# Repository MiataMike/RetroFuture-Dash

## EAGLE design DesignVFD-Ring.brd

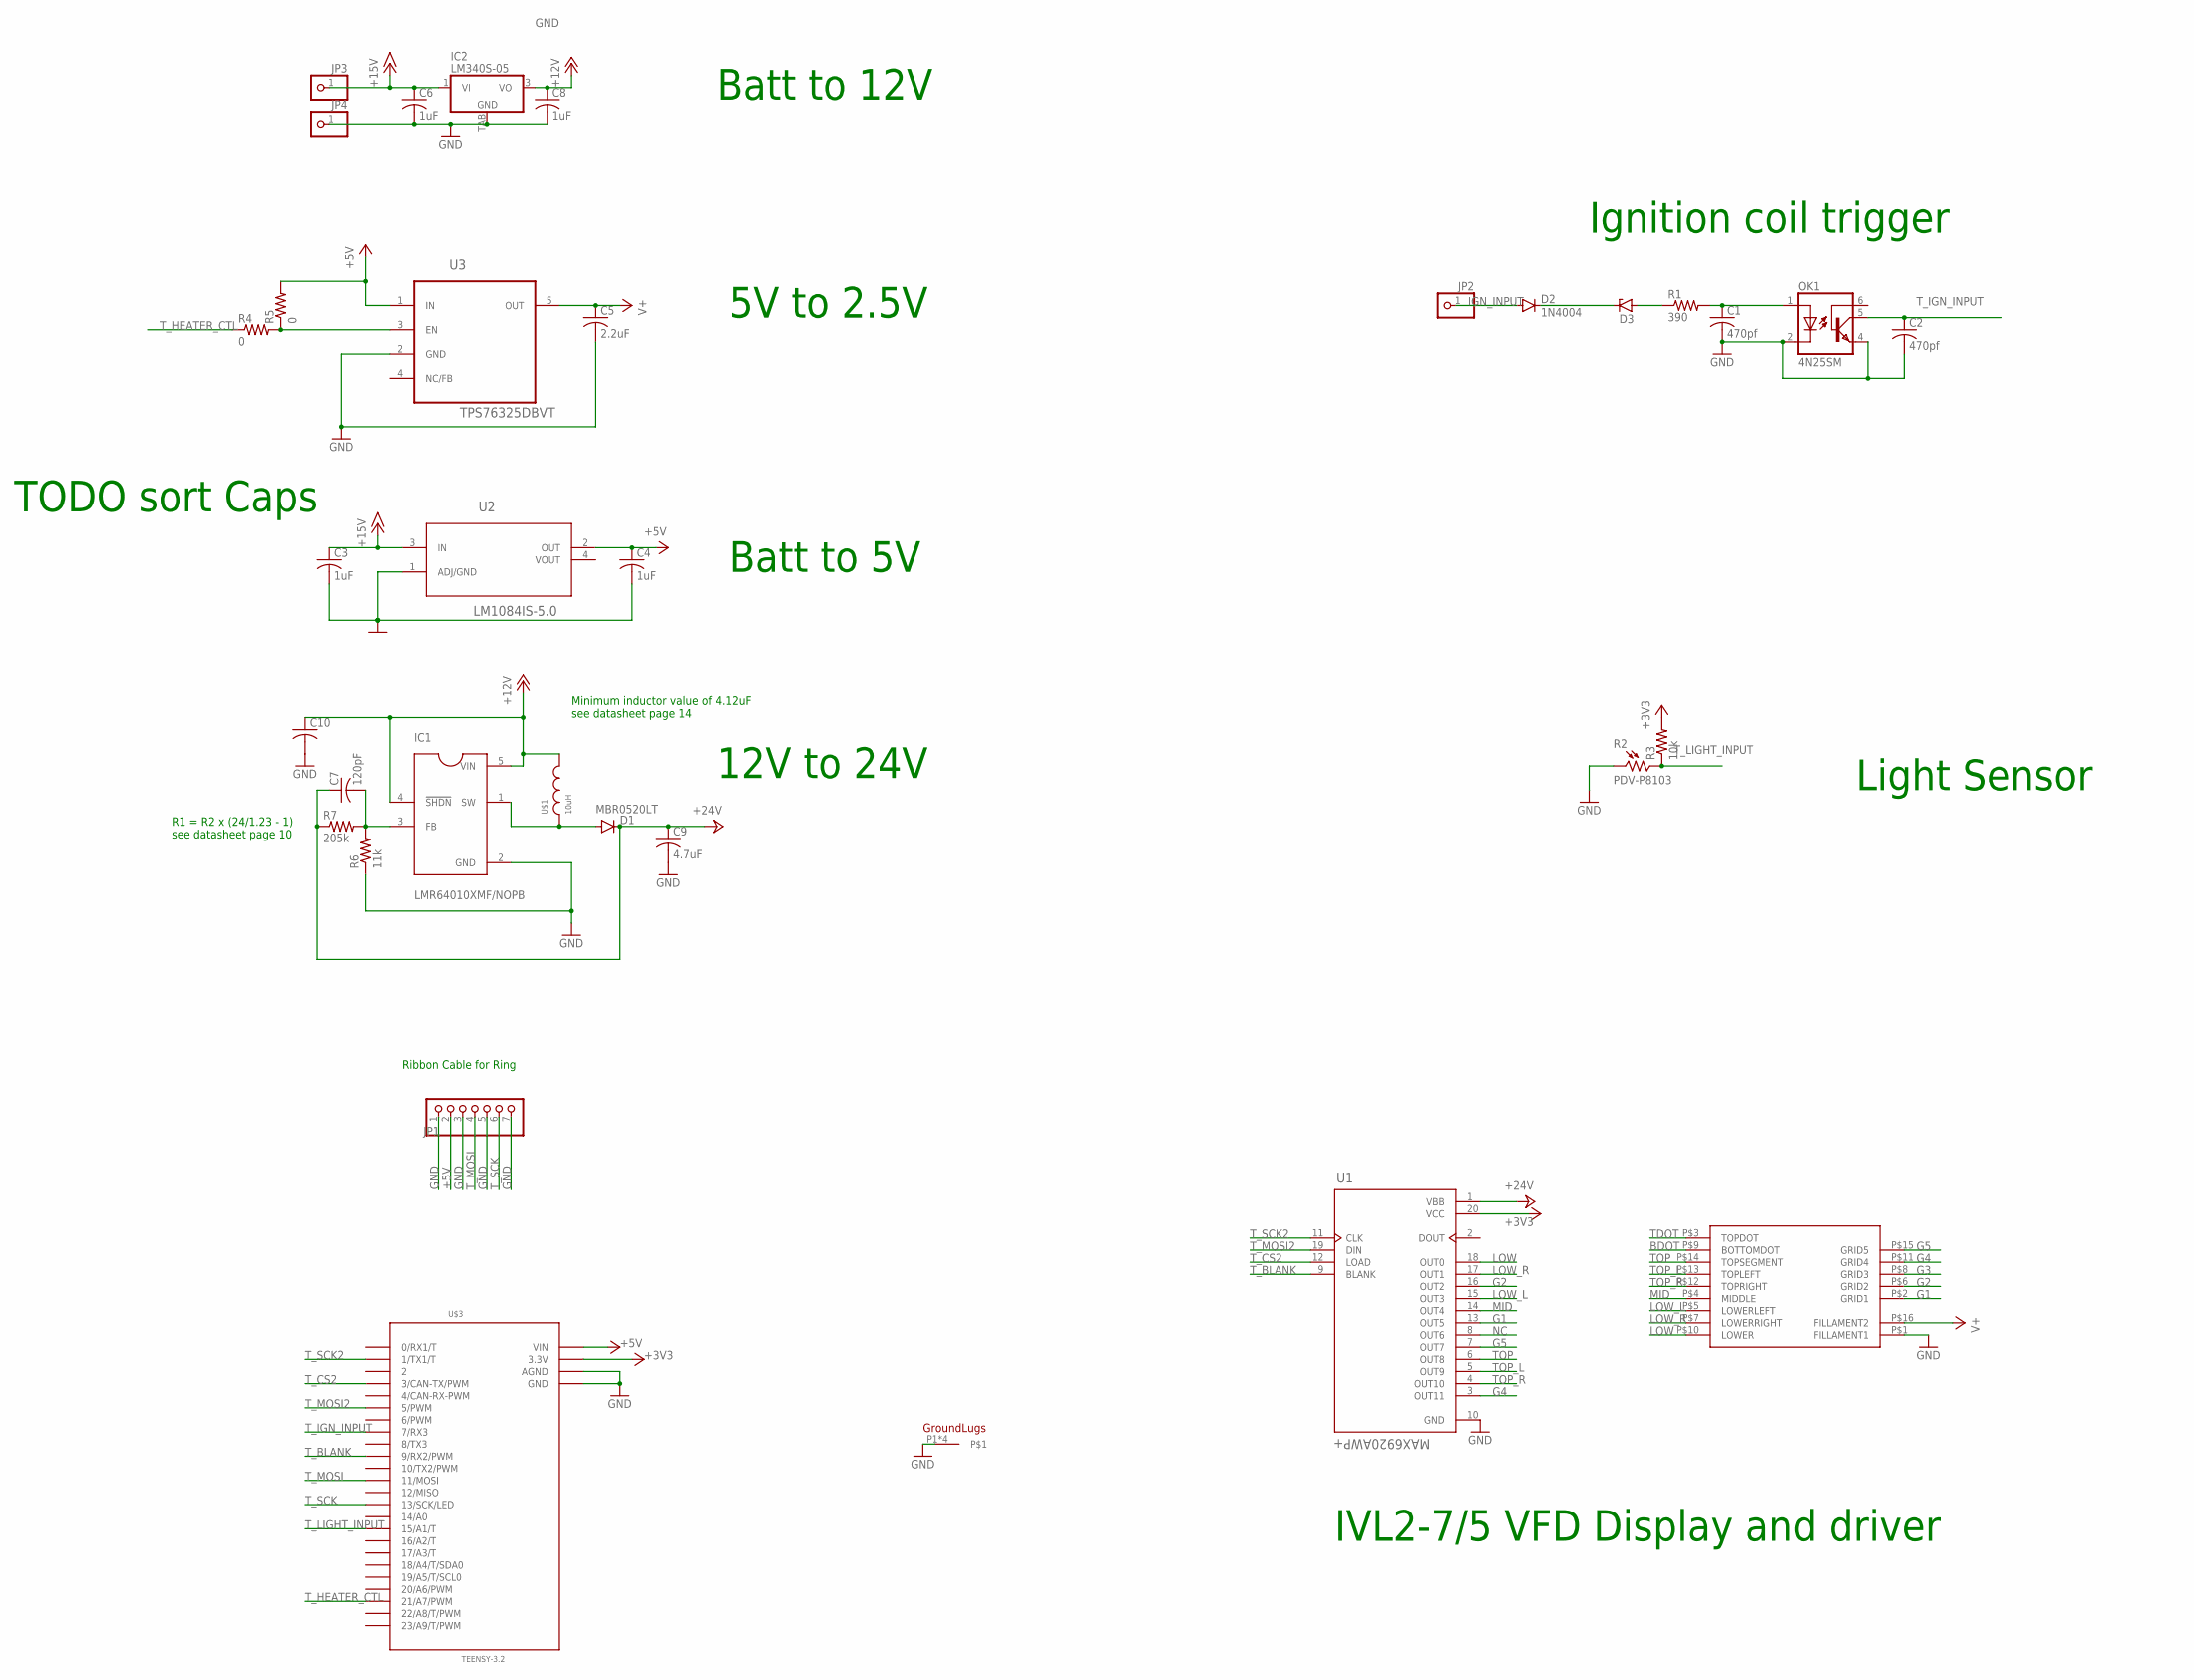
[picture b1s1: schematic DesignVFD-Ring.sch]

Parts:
C1, C2: 470pf; C0805
C3, C4, C6, C8: 1uF; C0805
C5: 2.2uF; C0805
C7: 120pF; C0805
C9: 4.7uF; C0805
C10: C-US025-050X050; C025-050X050
D1: MBR0520LT; SOD123
D2: 1N4004; DO41-10
D3: ZENER-DIODEDO41Z10; DO41Z10
IC1: LMR64010XMF/NOPB; SOT95P280X145-5N
IC2: LM340S-05; TO263-3
JP1: PINHD-1X7; 1X07
JP2, JP3, JP4: PINHD-1X1; 1X01
OK1: 4N25SM; DIL6-SMD
R1: 390; R0805
R2: PDV-P8103; PHODET_PDV-P8103
R3: 10k; R0805
R4, R5: 0; R0805
R6: 11k; R0805
R7: 205k; R0805
U1: MAX6920AWP+; SOIC127P1032X265-20N
U2: LM1084IS-5.0; TO254P1435X457-3N
U3: TPS76325DBVT; SOT95P280X145-5N
U$1: 10uH; 732-1416-ND
U$2: IVL2-7/5
U$3: TEENSY-3.2; TEENSY3.2
U$4: LUMINI3; STANDOFF-ELECTRICAL

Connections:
+3V3: R3.2, U1.20 (VCC), U$3.3V3+ (3.3V)
+5V: C4.1, JP1.2, R5.2, U2.2 (OUT), U3.1 (IN), U$3.VIN
+12V: C8.1, C10.1, IC1.4 (!SHDN), IC1.5 (VIN), IC2.3 (VO), U$1.P$2
+15V: C3.1, C6.1, IC2.1 (VI), JP3.1, U2.3 (IN)
+24V: C7.1, C9.1, D1.C, R7.1, U1.1 (VBB)
BDOT: U$2.P$9 (BOTTOMDOT)
G1: U1.13 (OUT5), U$2.P$2 (GRID1)
G2: U1.16 (OUT2), U$2.P$6 (GRID2)
G3: U$2.P$8 (GRID3)
G4: U1.3 (OUT11), U$2.P$11 (GRID4)
G5: U1.7 (OUT7), U$2.P$15 (GRID5)
GND: C1.2, C2.2, C3.2, C4.2, C5.2, C6.2, C8.2, C9.2, C10.2, IC1.2 (GND), IC2.TAB (GND), JP1.1, JP1.3, JP1.5, JP1.7, JP4.1, OK1.2 (C), OK1.4 (EMI), R2.1, R6.1, U1.10 (GND), U2.1 (ADJ/GND), U3.2 (GND), U$2.P$1 (FILLAMENT1), U$3.AGND, U$3.GND, U$4.P1, U$4.P2, U$4.P3, U$4.P4
IGN_INPUT: D2.A, JP2.1
LOW: U1.18 (OUT0), U$2.P$10 (LOWER)
LOW_L: U1.15 (OUT3), U$2.P$5 (LOWERLEFT)
LOW_R: U1.17 (OUT1), U$2.P$7 (LOWERRIGHT)
MID: U1.14 (OUT4), U$2.P$4 (MIDDLE)
unnamed: R4.2, R5.1, U3.3 (EN)
unnamed: D2.C, D3.C
unnamed: D3.A, R1.1
unnamed: C1.1, OK1.1 (A), R1.2
unnamed: D1.A, IC1.1 (SW), U$1.P$1
unnamed: C7.2, IC1.3 (FB), R6.2, R7.2
NC: U1.8 (OUT6)
TDOT: U$2.P$3 (TOPDOT)
TOP: U1.6 (OUT8), U$2.P$14 (TOPSEGMENT)
TOP_L: U1.5 (OUT9), U$2.P$13 (TOPLEFT)
TOP_R: U1.4 (OUT10), U$2.P$12 (TOPRIGHT)
T_BLANK: U1.9 (BLANK), U$3.9 (9/RX2/PWM)
T_CS2: U1.12 (LOAD), U$3.3 (3/CAN-TX/PWM)
T_HEATER_CTL: R4.1, U$3.21 (21/A7/PWM)
T_IGN_INPUT: C2.1, OK1.5 (COL), U$3.7 (7/RX3)
T_LIGHT_INPUT: R2.2, R3.1, U$3.15 (15/A1/T)
T_MOSI: JP1.4, U$3.11 (11/MOSI)
T_MOSI2: U1.19 (DIN), U$3.5 (5/PWM)
T_SCK: JP1.6, U$3.13 (13/SCK/LED)
T_SCK2: U1.11 (CLK), U$3.1 (1/TX1/T)
V+: C5.1, U3.5 (OUT), U$2.P$16 (FILLAMENT2)

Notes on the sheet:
Ribbon Cable for Ring
TODO sort Caps
Batt to 12V
5V to 2.5V
Batt to 5V
12V to 24V
Ignition coil trigger
IVL2-7/5 VFD Display and driver
Light Sensor
R1 = R2 x (24/1.23 - 1) see datasheet page 10
Minimum inductor value of 4.12uF see datasheet page 14

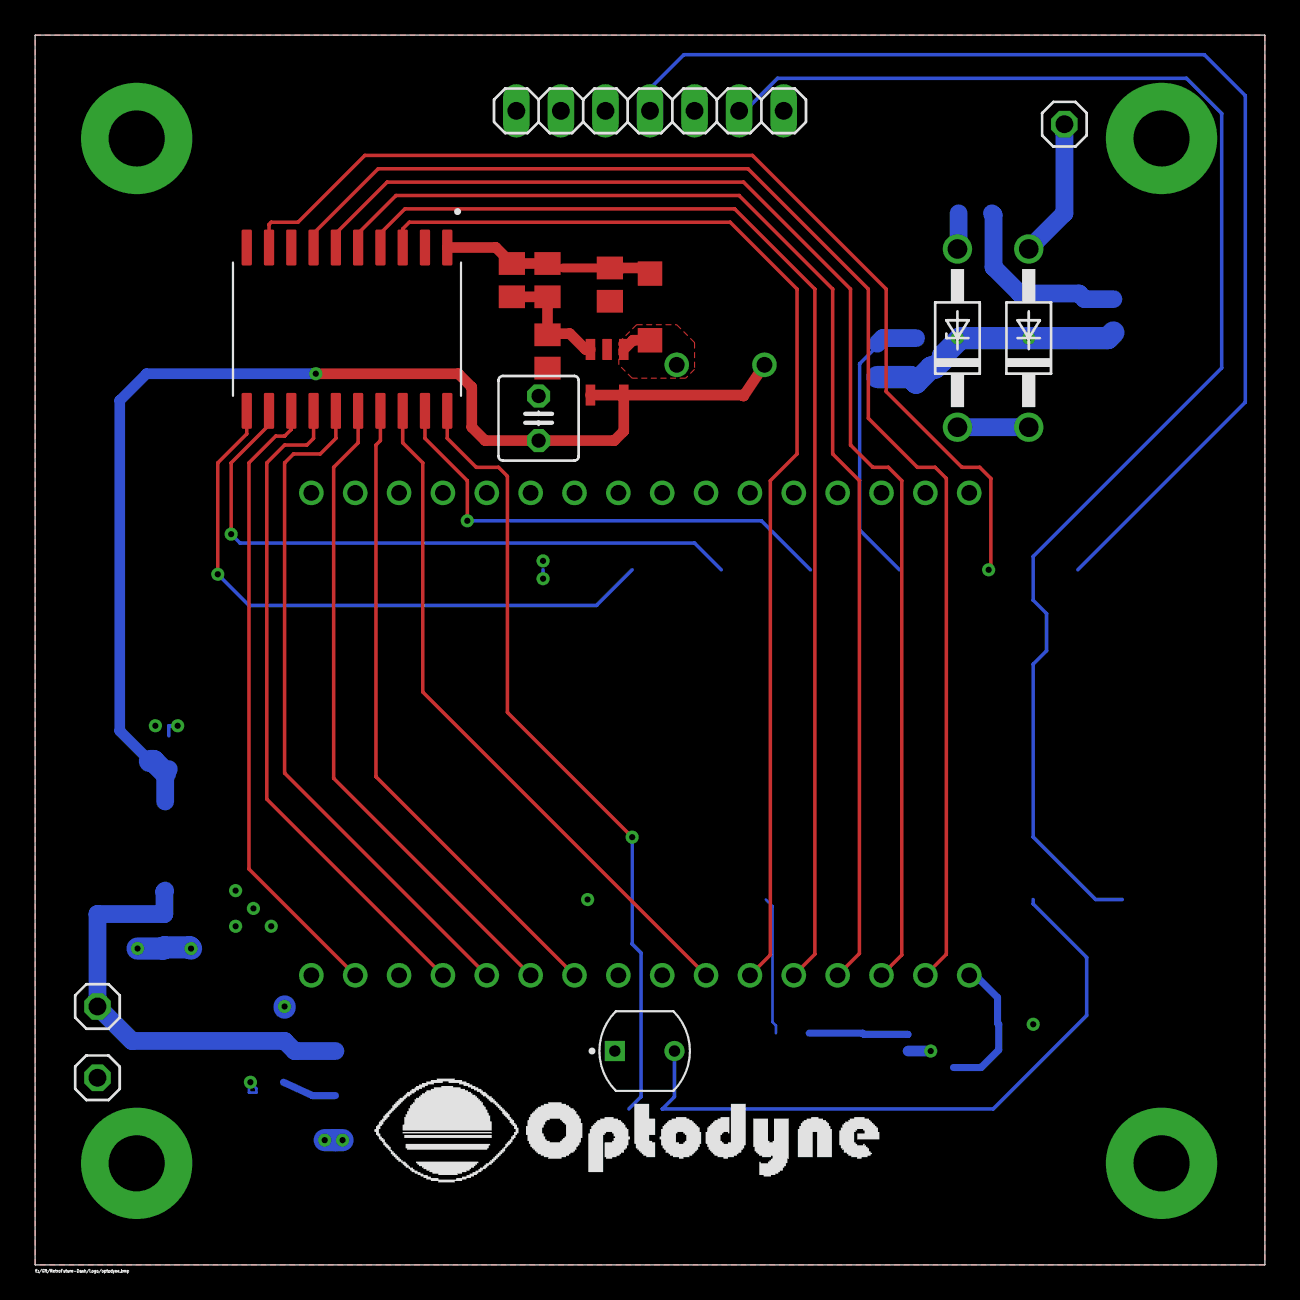
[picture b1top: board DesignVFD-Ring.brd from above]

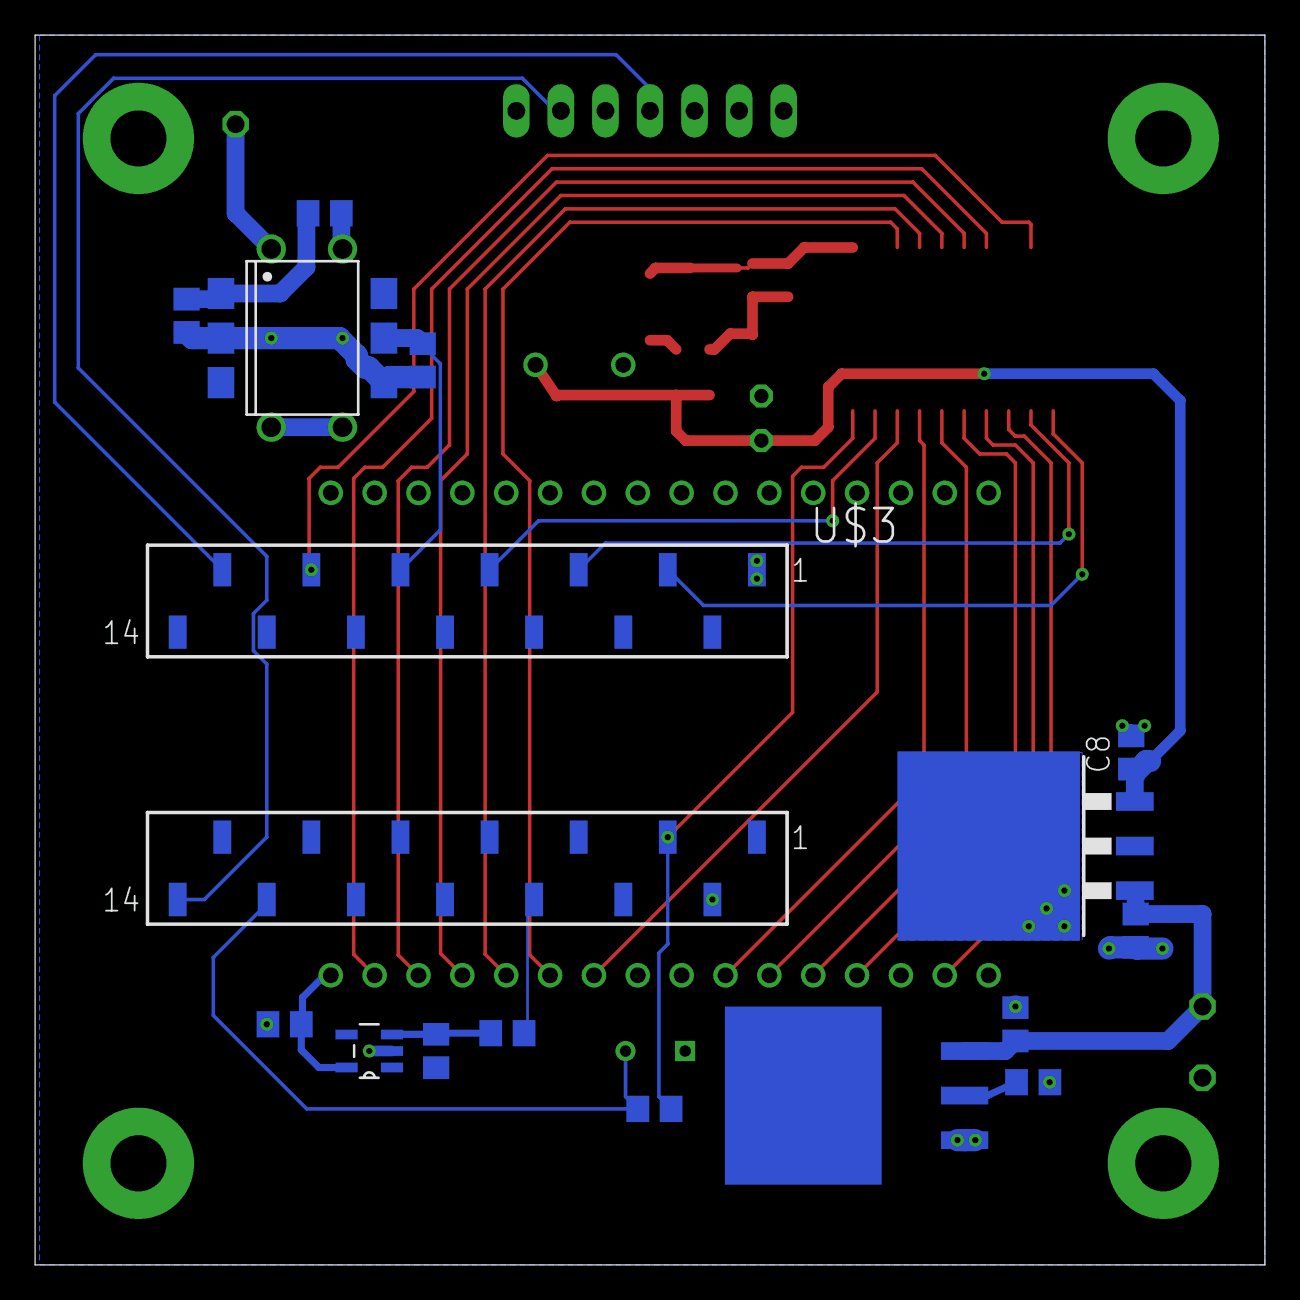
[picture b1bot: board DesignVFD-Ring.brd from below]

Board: 2 copper layers, 70.1 x 70.1 mm, 34 parts (16 on the bottom side), 34 nets.

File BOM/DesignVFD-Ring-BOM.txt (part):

Partlist exported from E:/Git/RetroFuture-Dash/DesignVFD-Ring.sch at 10/23/2019 11:31 PM

Part Value            Device                 Package              Description                                                                              AVAILABILITY DESCRIPTION                                                                                DIGI-KEY_PART_NUMBER DIGI-KEY_PURCHASE_URL                                                                                                                                            MF                MP               PACKAGE                    PRICE SPICEPREFIX
C1   470pf            C-USC0805              C0805                CAPACITOR, American symbol                                                                                                                                                                                                                                                                                                                                                                                                                                 C          
C2   470pf            C-USC0805              C0805                CAPACITOR, American symbol                                                                                                                                                                                                                                                                                                                                                                                                                                 C          
C3   1uF              C-USC0805              C0805                CAPACITOR, American symbol                                                                                                                                                                                                                                                                                                                                                                                                                                 C          
C4   1uF              C-USC0805              C0805                CAPACITOR, American symbol                                                                                                                                                                                                                                                                                                                                                                                                                                 C          
C5   2.2uF            C-USC0805              C0805                CAPACITOR, American symbol                                                                                                                                                                                                                                                                                                                                                                                                                                 C          
C6   1uF              C-USC0805              C0805                CAPACITOR, American symbol                                                                                                                                                                                                                                                                                                                                                                                                                                 C          
C7   120pF            C-USC0805              C0805                CAPACITOR, American symbol                                                                                                                                                                                                                                                                                                                                                                                                                                 C          
C8   1uF              C-USC0805              C0805                CAPACITOR, American symbol                                                                                                                                                                                                                                                                                                                                                                                                                                 C          
C9   4.7uF            C-USC0805              C0805                CAPACITOR, American symbol                                                                                                                                                                                                                                                                                                                                                                                                                                 C          
C10                   C-US025-050X050        C025-050X050         CAPACITOR, American symbol                                                                                                                                                                                                                                                                                                                                                                                                                                 C          
D1   MBR0520LT        MBR0520LT              SOD123               SCHOTTKY BARRIER RECTIFIER                                                                                                                                                                                                                                                                                                                                                                                                                                            
D2   1N4004           1N4004                 DO41-10              DIODE                                                                                                                                                                                                                                                                                                                                                                                                                                                                 
D3                    ZENER-DIODEDO41Z10     DO41Z10              Z-Diode                                                                                                                                                                                                                                                                                                                                                                                                                                                               
IC1  LMR64010XMF/NOPB LMR64010XMF/NOPB       SOT95P280X145-5N     SIMPLE SWITCHER? 2.7V to 14V, 1A Step-Up Regulator in SOT-23 Package 5-SOT-23 -40 to 125               SIMPLE SWITCHER? 2.7V to 14V, 1A Step-Up Regulator in SOT-23 Package 5-SOT-23 -40 to 125  296-38770-1-ND       https://www.digikey.com/product-detail/en/texas-instruments/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 Texas Instruments LMR64010XMF/NOPB SOT-23-5 Texas Instruments                  
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
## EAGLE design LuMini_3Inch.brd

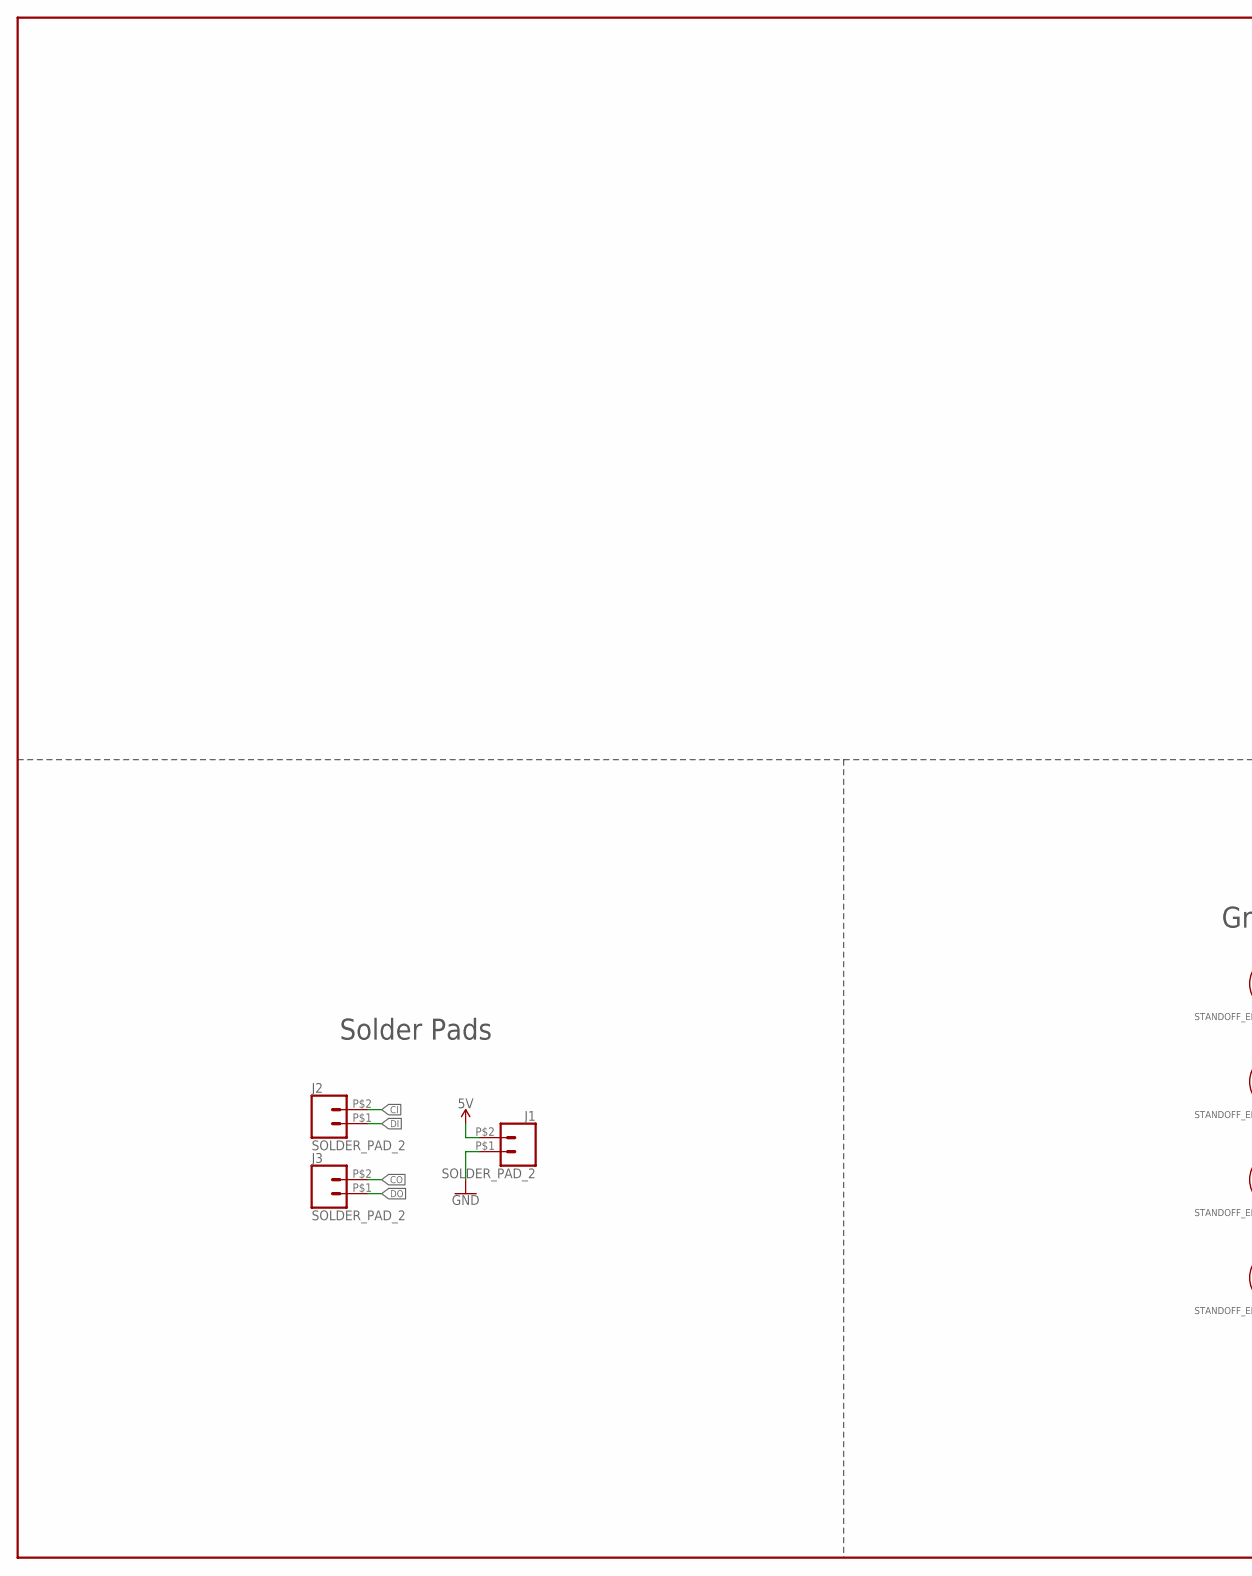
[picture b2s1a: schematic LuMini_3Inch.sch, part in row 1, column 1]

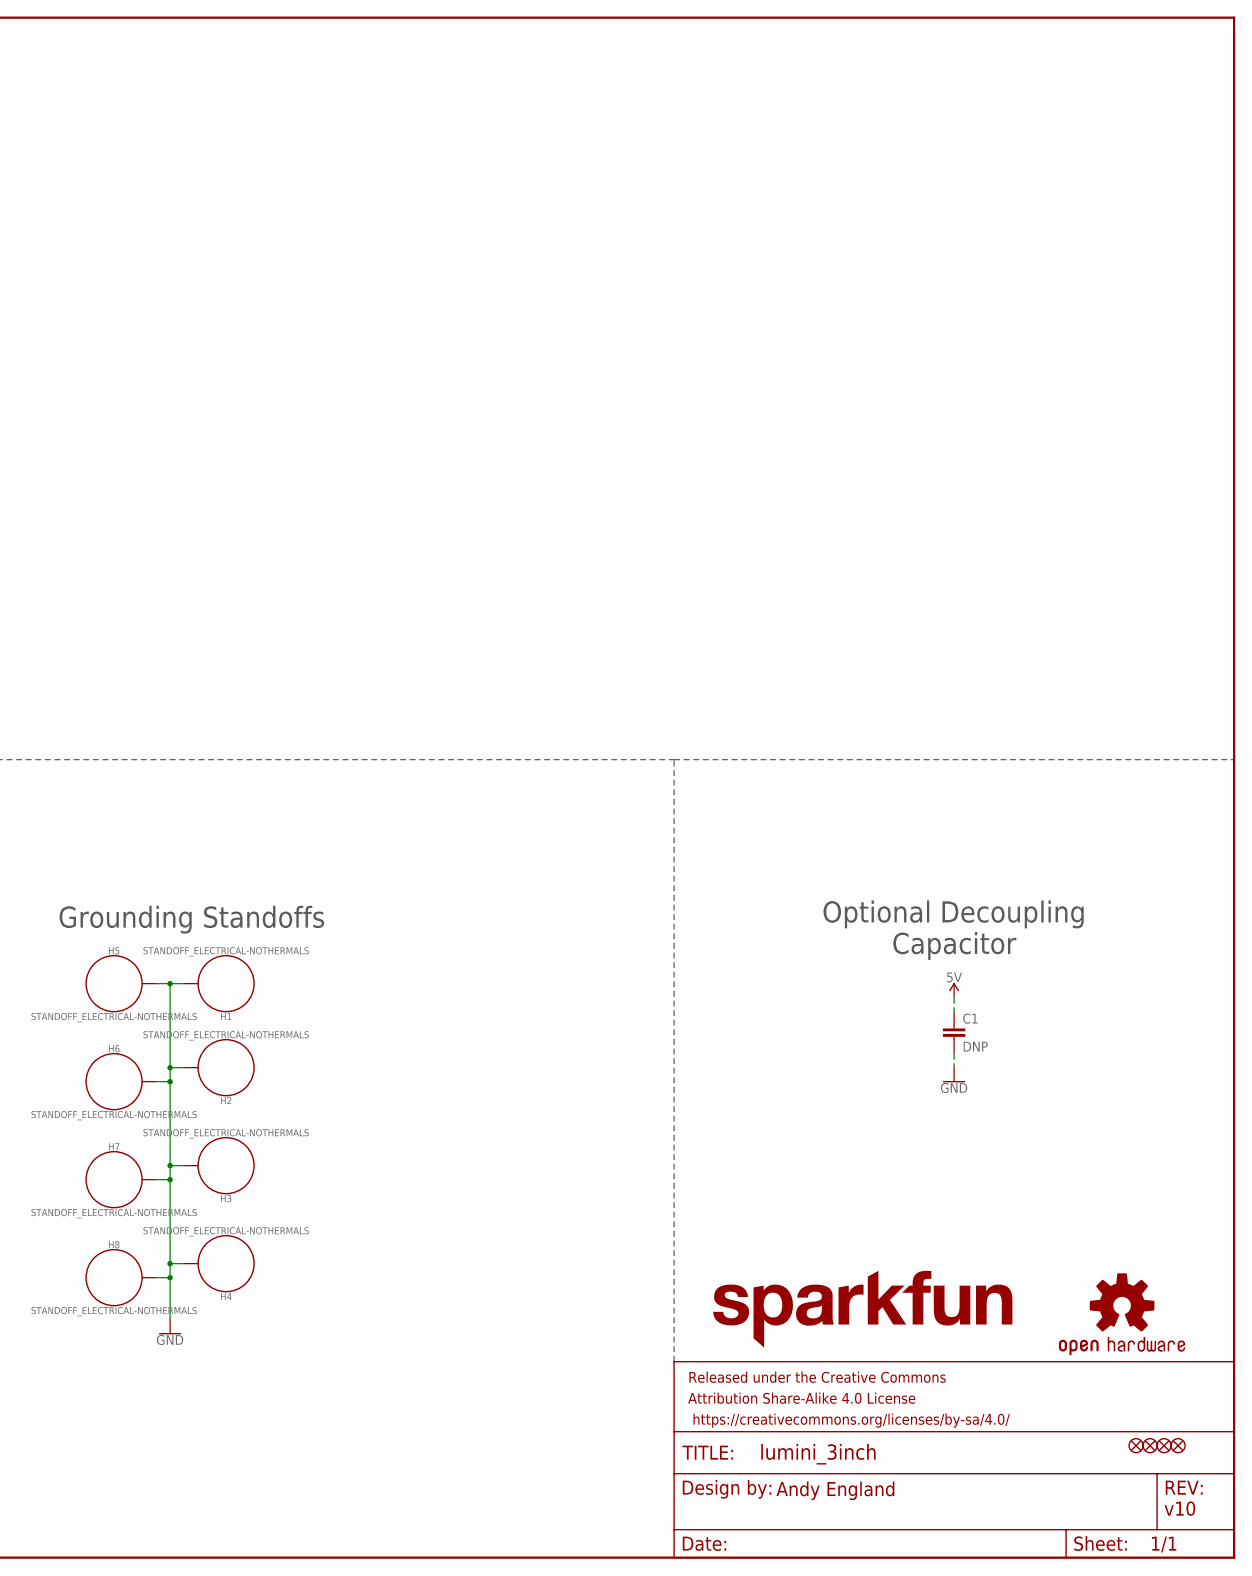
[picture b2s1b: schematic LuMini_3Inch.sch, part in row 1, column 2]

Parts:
C1: DNP; 1206
FD1, FD2, FD3, FD4: FIDUCIALUFIDUCIAL; FIDUCIAL-MICRO
FRAME1: FRAME-LEDGER; CREATIVE_COMMONS
H1, H2, H3, H4, H5, H6, H7, H8: STANDOFF_ELECTRICAL-NOTHERMALS; STANDOFF-ELECTRICAL-NOTHERMALS
J1, J2, J3: SOLDER_PAD_2
LOGO1: OSHW-LOGOS; OSHW-LOGO-S
LOGO2: SFE_LOGO_NAME.1_INCH; SFE_LOGO_NAME_.1

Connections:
5V: C1.1, J1.P$2 (2)
CI: J2.P$2 (2)
CO: J3.P$2 (2)
DI: J2.P$1 (1)
DO: J3.P$1 (1)
GND: C1.2, H1.P1, H2.P1, H3.P1, H4.P1, H5.P1, H6.P1, H7.P1, H8.P1, J1.P$1 (1)

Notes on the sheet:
Grounding Standoffs
Andy England
v10
Optional Decoupling Capacitor
Solder Pads

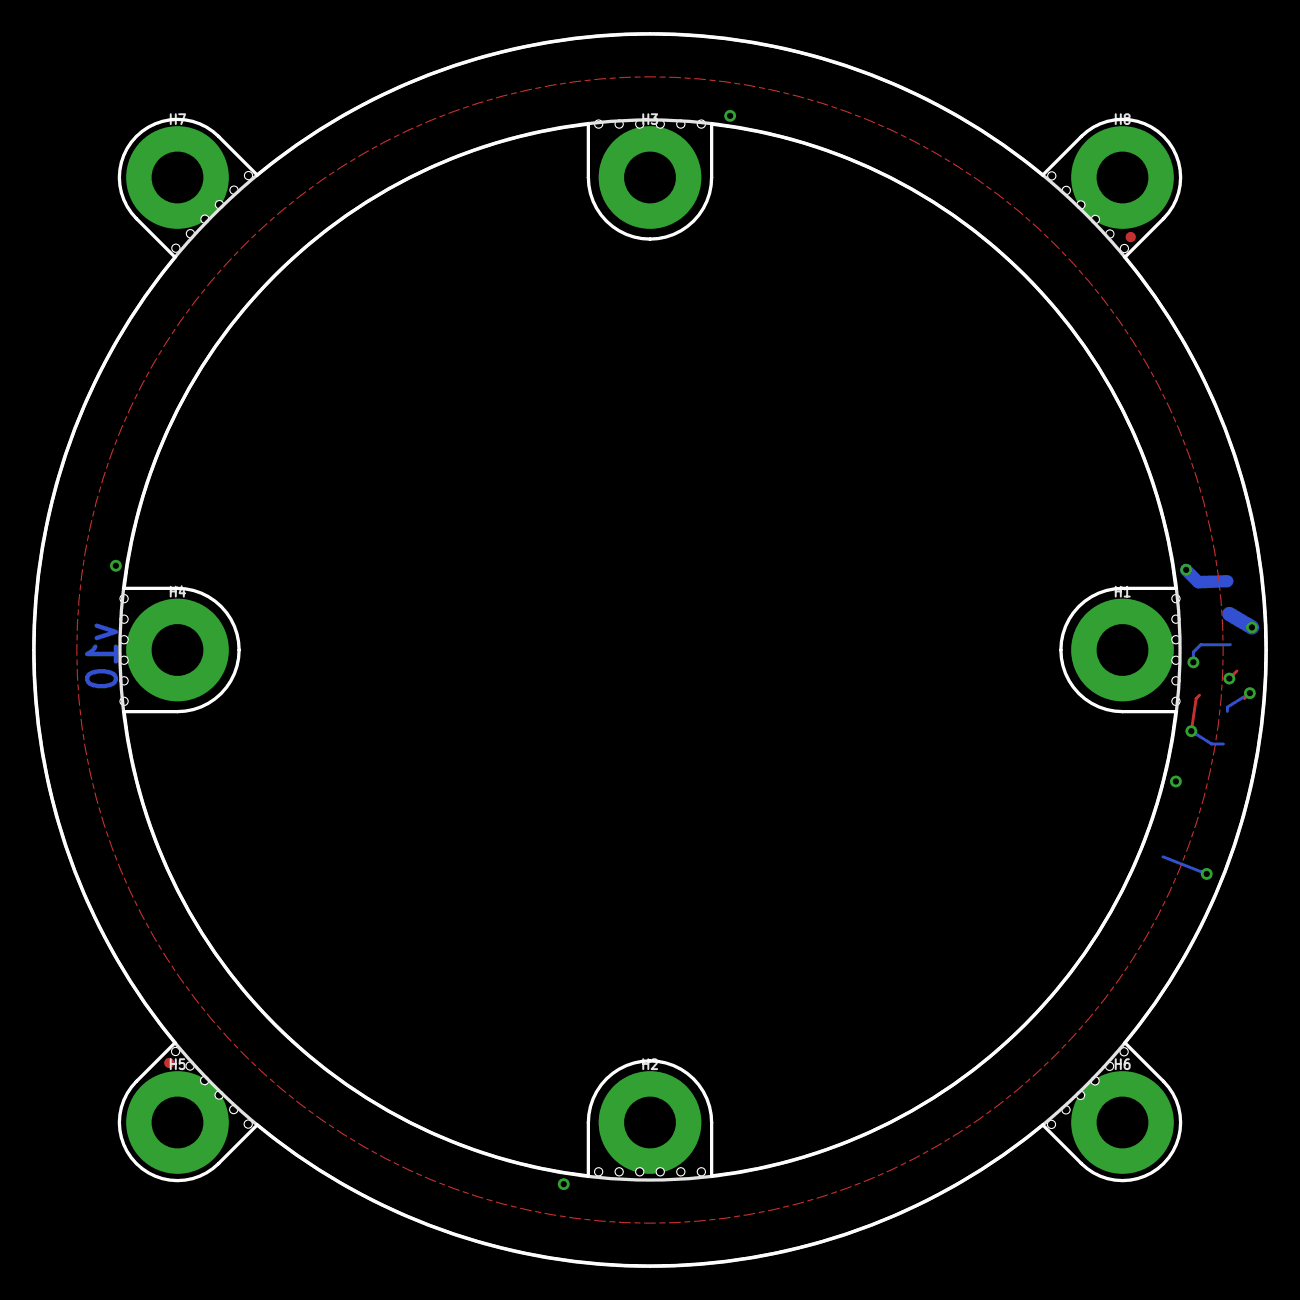
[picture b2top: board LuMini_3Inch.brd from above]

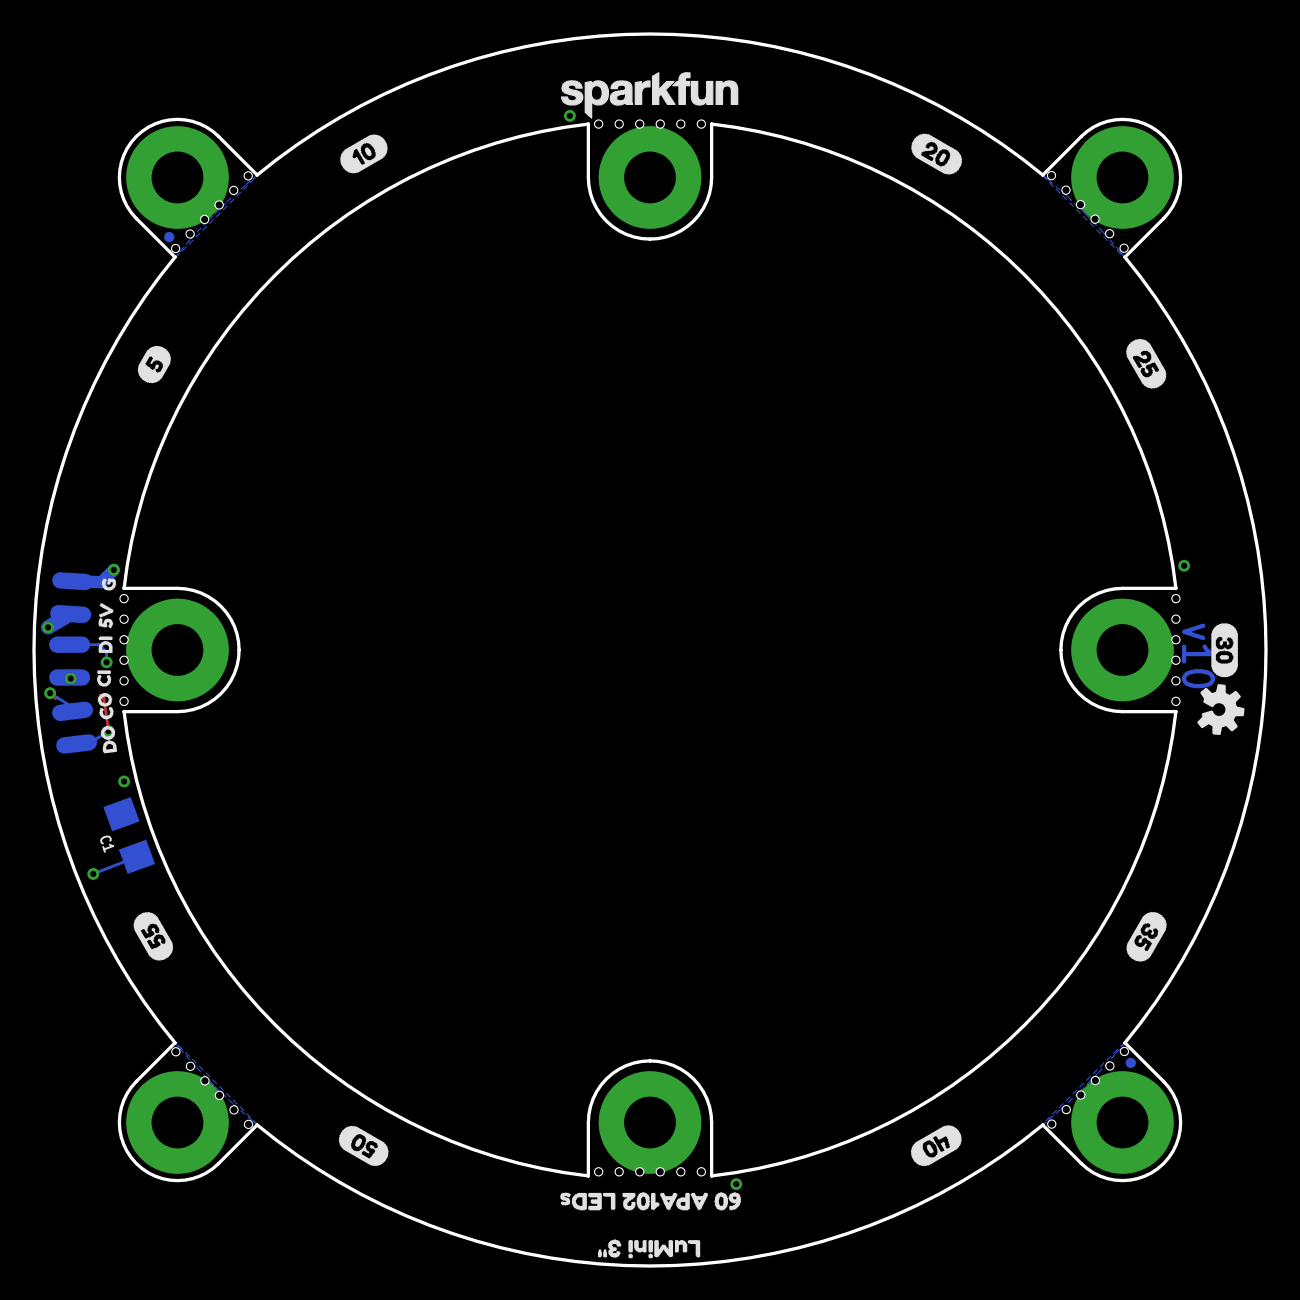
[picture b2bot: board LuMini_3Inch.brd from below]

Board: 2 copper layers, 76.2 x 76.2 mm, 37 parts (25 on the bottom side), 2 nets.

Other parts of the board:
U$1: LUMINI_3#2
U$2: 60_APA102_LEDS0
U$3: 54
U$4: 5V6
U$5: G4
U$6: 105
U$7: DO3
U$8: CO1
U$9: CI6
U$10: DI4
U$11: 207
U$12: 258
U$13: 309
U$14: 3510
U$15: 4011
U$16: 5013
U$17: 5514
U$18: ORDERING_INSTRUCTIONS

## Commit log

2019-10-19 Started Sch, added sockets for Teensy and Ring
2019-10-19 downloaded some spreadsheets, added most parts, finished ignition input
2019-10-19 Added IVL2/7-5
2019-10-19 Initial Schematic complete
2019-10-22 added 7th ribbon cable connection, verified SMPS values
2019-10-23 created layout, sorted
2019-10-24 24V reg layout
2019-10-24 Replaced headers with Teensy device
2019-10-24 Initial layout complete
2019-10-24 Fine tuned IVL location, added lumini docs
2019-10-24 added lumini ring
2019-10-24 about to repin IVL
2019-10-24 IVL complete
2019-10-24 Passed ERC and DRC!
2019-10-24 added aesthetic capacitor
2019-10-24 rotated inductor
2019-10-24 Saved $$ by reviewing BOM!
2019-10-24 added screws to bom
2019-10-25 created and added logo, removed board markings
2019-10-26 cleaned up a bit
2019-10-30 changed logo, updated gerbers and created budget pic
2019-11-22 TODO: try AC hack
2019-11-28 Made a start on the final code. Looks good
2019-12-02 added redline function
2021-05-27 Added RPM function after testing trigger
2021-05-27 updated RPM conversion
2023-04-23 added count method

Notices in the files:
parts and their libraries:
SparkFun-Aesthetics: Licensing: Creative Commons ShareAlike 4.0 International - https://creativecommons.org/licenses/by-sa/4.0
SparkFun-Aesthetics: Released under the Creative Commons Attribution Share-Alike 4.0 License
SparkFun-Aesthetics: https://creativecommons.org/licenses/by-sa/4.0
